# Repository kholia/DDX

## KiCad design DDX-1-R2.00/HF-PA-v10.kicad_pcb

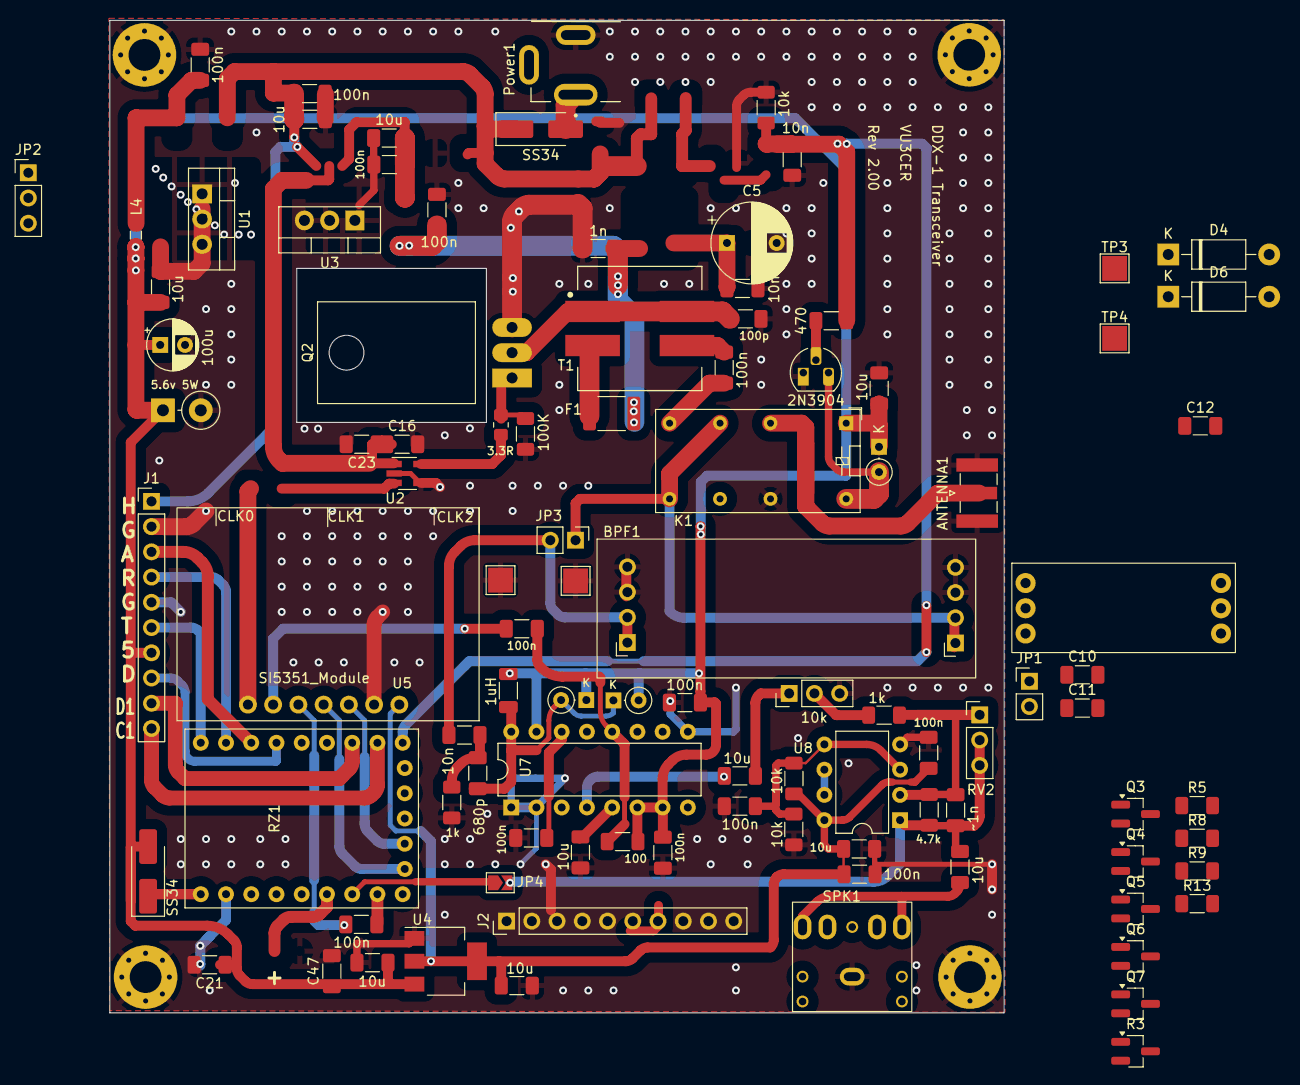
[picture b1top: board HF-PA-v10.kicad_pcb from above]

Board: 2 copper layers, 90.0 x 99.9 mm, 103 parts (0 on the bottom side), 61 nets.

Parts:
ANTENNA1: SMA; SMA_Samtec_SMA-J-P-X-ST-EM1_EdgeMount
BPF1: QRP_Filter; QRPLabs_Filter_TH
BPF2: Pluggable SMD BPF; Pluggable-BPF
C1, C7, C9, C21, C25, C26, C27, C28, C29, C30, C32, C37, C39, C41, C47: 100n; C_1206_3216Metric_Pad1.33x1.80mm_HandSolder
C2, C8, C12, C13, C16, C24, C36, C38, C42, C43, C45, C46: 10u; C_1206_3216Metric_Pad1.33x1.80mm_HandSolder
C3: 100p; C_1206_3216Metric_Pad1.33x1.80mm_HandSolder
C4, C6, C11, C23, C35: 10n; C_1206_3216Metric_Pad1.33x1.80mm_HandSolder
C5: 330u; CP_Radial_D8.0mm_P5.00mm
C10, C17: 1n; C_1206_3216Metric_Pad1.33x1.80mm_HandSolder
C31: 680p; C_1206_3216Metric_Pad1.33x1.80mm_HandSolder
C40: ~1n; C_1206_3216Metric_Pad1.33x1.80mm_HandSolder
C44: 100u; CP_Radial_D5.0mm_P2.50mm
D1, D2: SS34; D_SMA_Handsoldering
D3, D8, D9: 1N4148; D_DO-35_SOD27_P2.54mm_Vertical_KathodeUp
D4, D6: 1N4007; D_DO-41_SOD81_P10.16mm_Horizontal
D5: 5.6v 5W; D_DO-15_P3.81mm_Vertical_KathodeUp
F1: 2A; Fuse_1812_4532Metric_Pad1.30x3.40mm_HandSolder
H1, H2, H3, H4: MountingHole_Pad; MountingHole_3.2mm_M3_Pad_Via
J1: Conn_01x06; PinHeader_1x10_P2.54mm_Vertical
J2: E-LPF; PinHeader_1x10_P2.54mm_Vertical
JP1, JP3: Jumper_2_Open; PinHeader_1x02_P2.54mm_Vertical
JP2: Power_Switch; PinHeader_1x03_P2.54mm_Vertical
JP4: Jumper_2_Open; SolderJumper-2_P1.3mm_Open_TrianglePad1.0x1.5mm
K1: Omron G5V-2 / OEN 46-05-2C; Relay_DPDT_Omron_G5V-2
L4: Ferrite Bead (2A); L_0805_2012Metric_Pad1.05x1.20mm_HandSolder
L5: 1uH; L_1206_3216Metric_Pad1.22x1.90mm_HandSolder
Power1: DC-005 (Barrel Jack); XKB_DC-005-5A-2.0_Modded
Q1: 2N3904; TO-92_HandSolder
Q2: IRF510; TO-220-3_Horizontal_TabDown
Q3, Q4, Q5, Q6, Q7: BC847; SOT-23_Handsoldering
R1: 100K; R_1206_3216Metric_Pad1.30x1.75mm_HandSolder
R2, R10, R11: 10k; R_1206_3216Metric_Pad1.30x1.75mm_HandSolder
R3: 1k; SOT-23_Handsoldering
R4: 470; R_1206_3216Metric_Pad1.30x1.75mm_HandSolder
R5, R7, R8, R9, R13: 1k; R_1206_3216Metric_Pad1.30x1.75mm_HandSolder
R6: 100; R_1206_3216Metric_Pad1.30x1.75mm_HandSolder
R12: 3.3R; R_0805_2012Metric_Pad1.20x1.40mm_HandSolder
RV1: 10k; PinHeader_1x03_P2.54mm_Vertical
RV2: 20k; PinHeader_1x03_P2.54mm_Vertical
RZ1: RP2040-Zero
Rf1: 4.7k; R_1206_3216Metric_Pad1.30x1.75mm_HandSolder
Rin1: 1k; R_1206_3216Metric_Pad1.30x1.75mm_HandSolder
SPK1: SPEAKER; PJ-307_Modded
T1: Bifilar XFMR; IND_SRF1260A-4R7Y-Longer-Pads
TP1, TP2, TP3, TP4: TestPoint; TestPoint_Pad_2.5x2.5mm
U1: LM7805_TO220; TO-220-3_Vertical
U2: UCC27517ADBVR; SOT-23-5_HandSoldering
U3: LM7812_TO220; TO-220-3_Vertical
U4: AMS1117-3.3; SOT-223-3_TabPin2
U5: SI5351_Module; SI5351 Module
U7: CD2003GB_GP; DIP-16_W7.62mm
U8: MCP6002; DIP-8_W7.62mm

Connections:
10-11V: D6.1 (K), JP2.3 (B)
12V: C1.1, C2.1, C5.1, C6.1, C10.1, C11.1, C17.1, C32.1, D1.1 (K), F1.2, JP2.1 (A), U1.1 (VI), U3.1 (VI)
12V_VIA_LDO: C24.1, C30.1, D4.2 (A), J1.1, J2.6, U3.3 (VO)
15m: J2.1, Q3.3 (C)
20m: J2.2, Q4.3 (C)
40m: J2.3, Q5.3 (C)
80m: J2.4, Q6.3 (C)
+3.3V: C12.2, C25.1, C41.1, C42.1, C46.1, R10.1, U4.2 (VO), U5.1 (VIN), U8.8 (V+)
+5V: C8.1, C13.1, C21.1, C28.1, C37.1, C44.1, C45.1, C47.1, D2.2 (A), D3.1 (K), D5.1 (K), D8.1 (K), D9.2 (A), J1.7, J2.8, K1.1, L4.1, L5.2, R6.2, U4.3 (VI), U7.6 (VCC), U7.7 (AM_IF), U7.15 (FM_TUNER)
+VDC: D1.2 (A), Power1.1
/DRAIN: C3.1, Q2.2 (D), T1.1, T1.4
ANTENNA1: ANTENNA1.1 (In), K1.4, TP3.1
CAL: C27.2, RZ1.16 (GP15)
EXTRA: J2.5, Q7.3 (C)
G1: R3.1, RZ1.5 (GP4)
G2: R5.1, RZ1.6 (GP5)
G3: R8.1, RZ1.7 (GP6)
G4: R9.1, RZ1.8 (GP7)
G5: R13.1, RZ1.9 (GP8)
GND: ANTENNA1.2 (Ext), BPF1.3 (GND), BPF1.4 (GND), BPF1.5 (GND), BPF1.6 (GND), BPF2.3 (GND), BPF2.6 (GND), C1.2, C2.2, C3.2, C4.2, C5.2, C6.2, C8.2, C9.2, C10.2, C11.2, C12.1, C13.2, C16.2, C17.2, C21.2, C23.2, C24.2, C25.2, C28.2, C29.1, C30.2, C32.2, C36.2, C37.2, C39.2, C41.2, C42.2, C44.2, C45.2, C46.2, C47.2, D5.2 (A), H1.1, H2.1, H3.1, H4.1, J1.2, J1.5, J2.7, K1.13, Power1.2, Q1.1 (E), Q2.3 (S), Q3.2 (E), Q4.2 (E), Q5.2 (E), Q6.2 (E), Q7.2 (E), R1.2, R2.2, R7.2, R11.2, RV1.3, RZ1.23 (GND), SPK1.S, TP1.1, TP2.1, TP4.1, U1.2 (GND), U2.2 (GND), U2.4 (IN-), U3.2 (GND), U4.1 (GND), U5.2 (GND), U7.1 (FM_RF_IN), U7.2 (GND_IN), U7.9 (GND_OUT), U8.4 (V-)
LDATA: J1.8, RZ1.4 (GP3)
unnamed: C7.2, T1.3
unnamed: C31.1, C35.1, R7.1
unnamed: C38.2, RV1.1
unnamed: C43.2, SPK1.R, SPK1.T
unnamed: D2.1 (K), RZ1.22 (5V)
unnamed: D3.2 (A), K1.16, Q1.3 (C)
unnamed: D4.1 (K), D6.2 (A)
unnamed: C31.2, D8.2 (A), D9.1 (K), L5.1, U7.16 (AM_RF_IN)
unnamed: F1.1, T1.2
unnamed: C16.1, C23.1, JP2.2 (C), U2.1 (VDD)
unnamed: JP4.1 (A), RZ1.17 (GP26)
unnamed: Q1.2 (B), R4.2
unnamed: Q2.1 (G), R1.1, R12.2
unnamed: Q3.1 (B), R3.2
unnamed: Q4.1 (B), R5.2
unnamed: Q5.1 (B), R8.2
unnamed: Q6.1 (B), R9.2
unnamed: Q7.1 (B), R13.2
unnamed: RV1.2, Rin1.2
unnamed: C9.1, L4.2, U1.3 (VO)
unnamed: R12.1, U2.5 (OUT)
unnamed: C27.1, U5.5 (S2)
unnamed: C26.1, R6.1, U7.12 (AM_OSC)
unnamed: C29.2, U7.14 (FM/AM_SW)
unnamed: C39.1, R10.2, R11.1, U8.3 (+), U8.5 (+)
unnamed: C40.2, RV2.1, Rf1.2, Rin1.1, U8.2 (-)
unnamed: U8.6 (-), U8.7
PTT: C4.1, R2.1, R4.1, RZ1.10 (GP9)
RF_OUT1: C7.1, K1.8
RX: BPF1.1 (IN), BPF1.2 (IN), BPF2.1 (ANT), BPF2.2 (ANT), JP1.1 (A), JP3.1 (A), K1.6, K1.9
RX_AFTER_HPF: BPF1.7 (OUT), BPF1.8 (OUT), BPF2.4 (RF), BPF2.5 (RF), C35.2, JP1.2 (B), JP3.2 (B)
RX_AUDIO: C36.1, C38.1, U7.4 (AM_MIX), U7.5 (AGC)
RX_OSC: C26.2, U5.6 (S1)
SCL: RZ1.14 (GP13), U5.4 (SCL)
SDA: RZ1.13 (GP12), U5.3 (SDA)
TO_ADC: C40.1, C43.1, JP4.2 (B), RV2.2, RV2.3, Rf1.1, U8.1
TUNE: J1.3, RZ1.3 (GP2)
TX_RF: U2.3 (IN+), U5.7 (SO)
UART_RX: J1.4, RZ1.2 (GP1)
UART_TX: J1.6, RZ1.1 (GP0)
